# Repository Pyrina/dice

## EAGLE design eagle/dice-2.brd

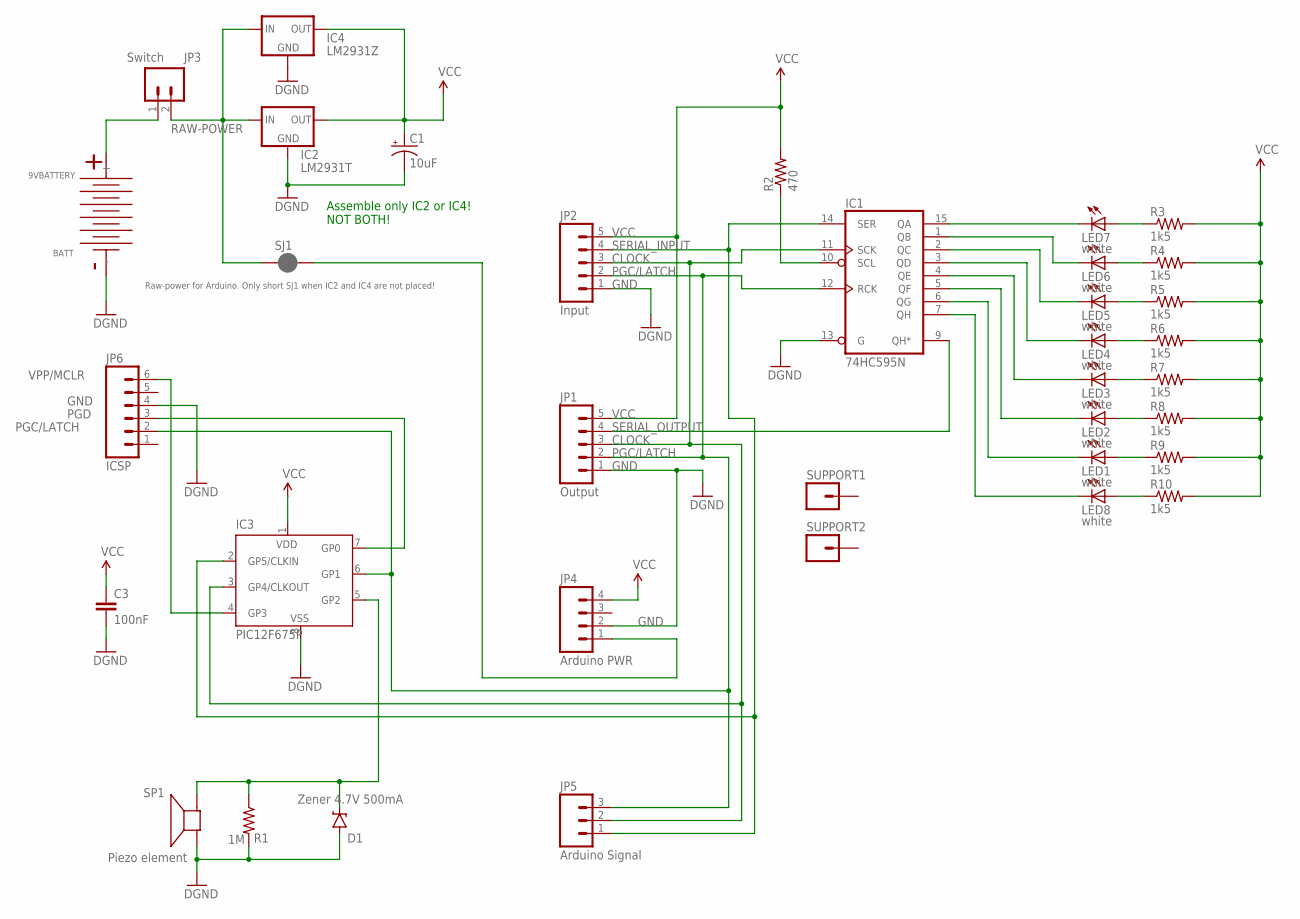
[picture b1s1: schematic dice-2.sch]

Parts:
BATT: 9VBATTERY; 9V-BATTERY-HOLDER
C1: 10uF; CPOL-RADIAL-10UF-25V
C3: 100nF; CAP-PTH-5MM
D1: Zener 4.7V 500mA; DIODE-ZENER
IC1: 74HC595N; DIL16
IC2: LM2931T; TO220S
IC3: PIC12F675P; DIL8
IC4: LM2931Z; TO92
JP1: Output; 1X05
JP2: Input; 1X05
JP3: Switch; 1X02
JP4: Arduino PWR; 1X04
JP5: Arduino Signal; 1X03
JP6: ICSP; 1X06-SIP_LOCK
LED1, LED2, LED3, LED4, LED5, LED6, LED7, LED8: white; LED5MM
R1: 1M; AXIAL-0.4
R2: 470; AXIAL-0.4
R3, R4, R5, R6, R7, R8, R9, R10: 1k5; AXIAL-0.4
SJ1: Raw-power for Arduino. Only short SJ1 when IC2 an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; PAD-JUMPER-2-NC_BY_PASTE_YES_SILK
SP1: Piezo element; PS12
SUPPORT1, SUPPORT2: M01PTH; 1X01

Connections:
CLOCK: IC1.11 (SCK), IC3.3 (GP4/CLKOUT), JP1.3, JP2.3, JP5.2
GND: BATT.-, C1.2 (-), C3.2, D1.P$2 (A), IC1.8 (GND), IC1.13 (G), IC2.2 (GND), IC3.8 (VSS), IC4.2 (GND), JP1.1, JP2.1, JP4.2, JP6.4, R1.P$2 (2), SP1.P$1 (+)
unnamed: IC1.15 (QA), LED7.K (C)
unnamed: IC1.1 (QB), LED6.K (C)
unnamed: IC1.5 (QF), LED2.K (C)
unnamed: IC1.2 (QC), LED5.K (C)
unnamed: IC1.3 (QD), LED4.K (C)
unnamed: IC1.4 (QE), LED3.K (C)
unnamed: LED6.A, R4.P$1 (1)
unnamed: IC1.6 (QG), LED1.K (C)
unnamed: LED7.A, R3.P$1 (1)
unnamed: LED5.A, R5.P$1 (1)
unnamed: LED4.A, R6.P$1 (1)
unnamed: LED3.A, R7.P$1 (1)
unnamed: LED1.A, R9.P$1 (1)
unnamed: BATT.+, JP3.1
unnamed: IC1.7 (QH), LED8.K (C)
unnamed: LED8.A, R10.P$1 (1)
unnamed: IC1.10 (SCL), R2.P$1 (1)
unnamed: D1.P$1 (C), IC3.5 (GP2), R1.P$1 (1), SP1.P$2 (-)
unnamed: JP4.1, SJ1.2
unnamed: LED2.A, R8.P$1 (1)
PGC/LATCH: IC1.12 (RCK), IC3.6 (GP1), JP1.2, JP2.2, JP5.3, JP6.2
PGD: IC3.7 (GP0), JP6.3
RAW-POWER: IC2.1 (IN), IC4.3 (IN), JP3.2, SJ1.1
SERIAL_INPUT: IC1.14 (SER), IC3.2 (GP5/CLKIN), JP2.4, JP5.1
SERIAL_OUTPUT: IC1.9 (QH*), JP1.4
VCC: C1.1 (+), C3.1, IC1.16 (VCC), IC2.3 (OUT), IC3.1 (VDD), IC4.1 (OUT), JP1.5, JP2.5, JP4.4, R2.P$2 (2), R3.P$2 (2), R4.P$2 (2), R5.P$2 (2), R6.P$2 (2), R7.P$2 (2), R8.P$2 (2), R9.P$2 (2), R10.P$2 (2)
VPP/MCLR: IC3.4 (GP3), JP6.6

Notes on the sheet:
Assemble only IC2 or IC4! NOT BOTH!

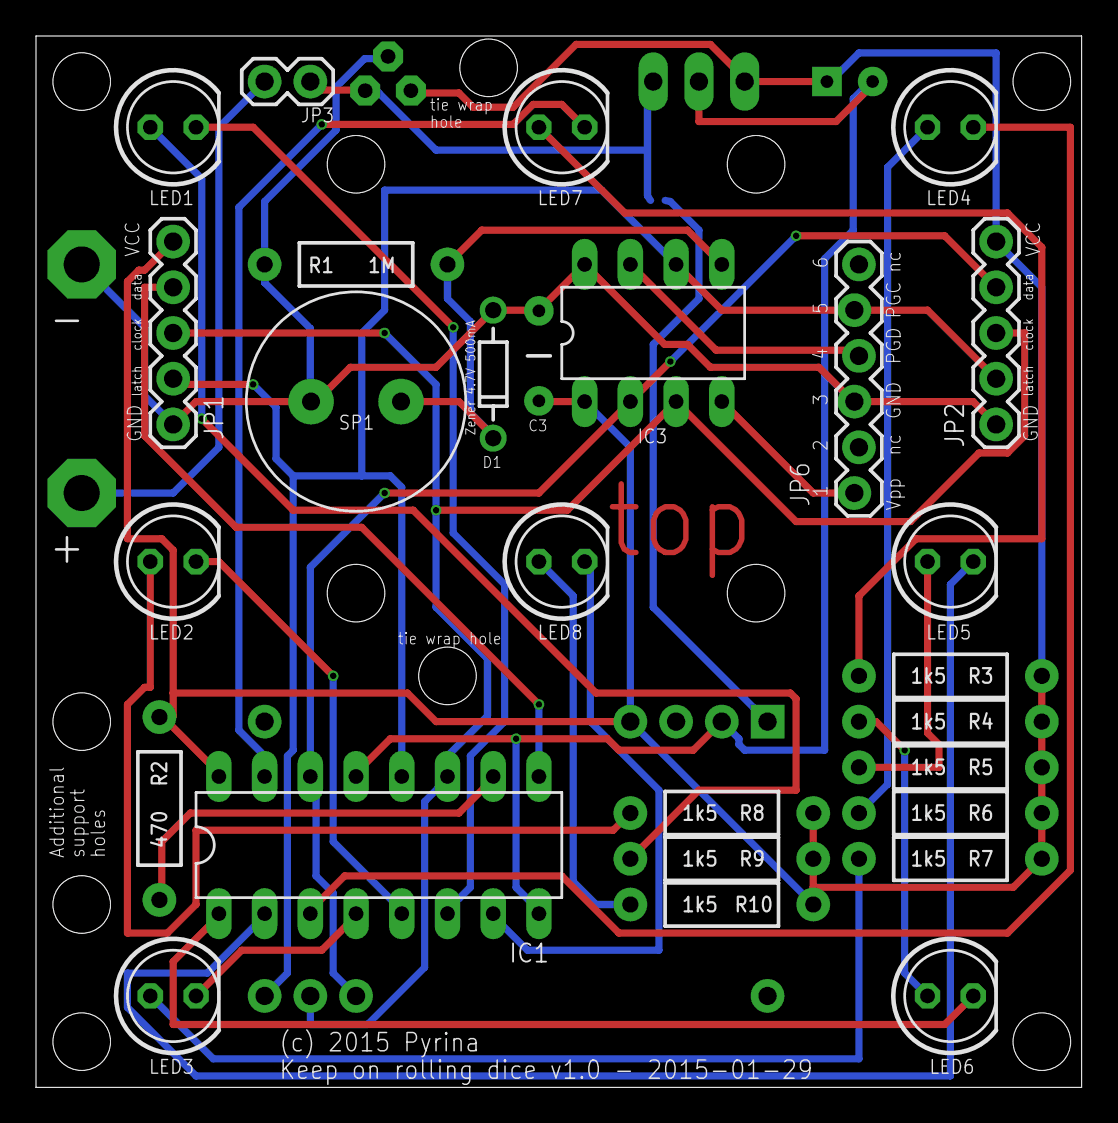
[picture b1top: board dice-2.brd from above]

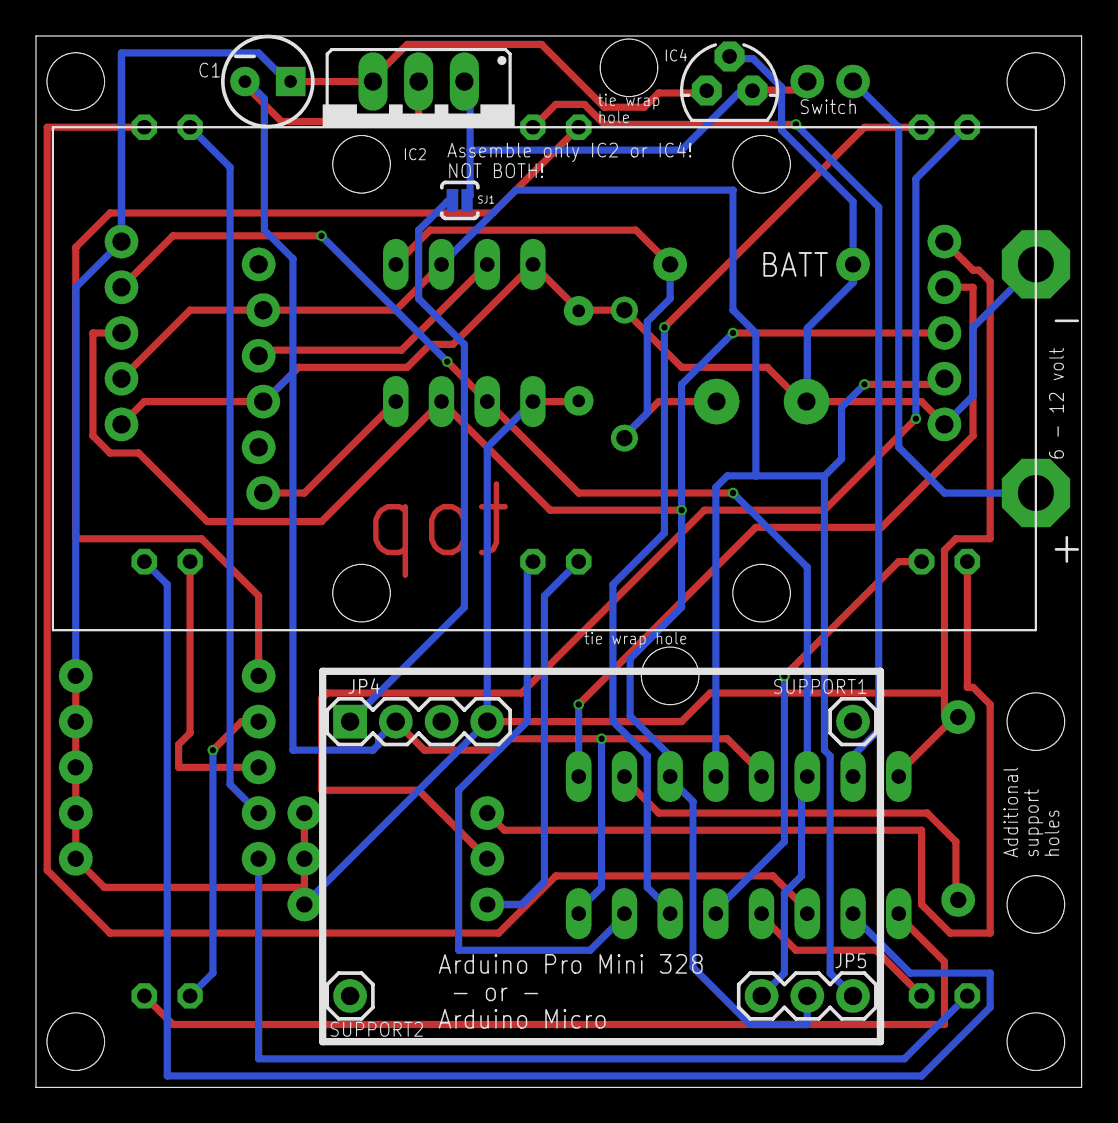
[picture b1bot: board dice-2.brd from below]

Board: 2 copper layers, 58.1 x 58.4 mm, 36 parts (9 on the bottom side), 29 nets.

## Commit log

2015-04-01 Added Eagle files for the dice

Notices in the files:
eagle/dice-2.brd:
(c) 2015 Pyrina
parts and their libraries:
SparkFun-Connectors: Licensing: Creative Commons ShareAlike 4.0 International - https://creativecommons.org/licenses/by-sa/4.0
